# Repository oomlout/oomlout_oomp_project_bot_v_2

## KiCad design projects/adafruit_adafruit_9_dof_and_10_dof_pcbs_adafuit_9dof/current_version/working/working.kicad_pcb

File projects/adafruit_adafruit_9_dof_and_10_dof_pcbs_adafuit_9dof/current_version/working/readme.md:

# adafruit_9_dof_and_10_dof_pcbs
 
## summary 
* id: adafruit_adafruit_9_dof_and_10_dof_pcbs_adafuit_9dof
* user: adafruit
* name: adafruit_9_dof_and_10_dof_pcbs
* board: adafuit_9dof
* repo: https://github.com/adafruit/Adafruit-9-DOF-and-10-DOF-PCBs

* src_file_repo_sch: 
* src_file_repo_sch_link: https://github.com/adafruit/Adafruit-9-DOF-and-10-DOF-PCBs/tree/master/
* full details link: https://github.com/oomlout/oomlout_oomp_project_bot_v_2/tree/main/projects/adafruit_adafruit_9_dof_and_10_dof_pcbs_adafuit_9dof/current_version/working  

## schematic  
  
[schematic (pdf)](working_schematic.pdf) 

## pcb  

[board (pdf)](working.pdf)  

## working_bom
| Id | Designator | Footprint | Quantity | Designation | Supplier and ref |  | None | 
| --- | --- | --- | --- | --- | --- | --- | --- | 
| 1 | C3,C4 | _0805MP | 2 | 0.1uF |  |  | [''] | 
| 2 | FID3,FID2,FID1 | FIDUCIAL_1MM | 3 | FIDUCIAL" |  |  | [''] | 
| 3 | R2,R1,R4,R5,R3,R7,R6 | _0805MP | 7 | 10K |  |  | [''] | 
| 4 | U1 | L3G4200D_LGA16L | 1 | L3GD20 |  |  | [''] | 
| 5 | U$30,U$29,U$31,U$28 | MOUNTINGHOLE_2.5_PLATED_THICK | 4 | MOUNTINGHOLE2.5_THICK |  |  | [''] | 
| 6 | U$32 | ADAFRUIT_3.5MM | 1 |  |  |  | [''] | 
| 7 | Q1,Q2 | SOT23-WIDE | 2 | BSS138 |  |  | [''] | 
| 8 | C2 | _0805MP | 1 | 470nF |  |  | [''] | 
| 9 | U$25 | SYMBOL_GYROXYZ_10MM | 1 |  |  |  | [''] | 
| 10 | JP1 | 1X10_ROUND | 1 |  |  |  | [''] | 
| 11 | C8,C9,C5 | _0805MP | 3 | 10uF |  |  | [''] | 
| 12 | U4 | SOT23-5 | 1 | MIC5225-3.3 |  |  | [''] | 
| 13 | U2 | LGA14 | 1 | LSM303DLHC |  |  | [''] | 
| 14 | U3 | BMP180_EXTENDED | 1 | BMP180 |  |  | [''] | 
| 15 | C7 | _0805MP | 1 | 0.22ÂµF |  |  | [''] | 
| 16 | C6 | _0805MP | 1 | 4.7uF |  |  | [''] | 
| 17 | C1 | _0805MP | 1 | 10nF |  |  | [''] | 
| 18 | U$26 | ADAFRUIT_TEXT_20MM | 1 |  |  |  | [''] | 

## bom_schematic
| Ref | Qnty | Value | Cmp name | Footprint | Description | Vendor | DNP | 
| --- | --- | --- | --- | --- | --- | --- | --- | 
| C1 | 1 | 10nF | CAP_CERAMIC_0805MP | working:_0805MP |  |  |  | 
| C2 | 1 | 470nF | CAP_CERAMIC_0805MP | working:_0805MP |  |  |  | 
| C3, C4 | 2 | 0.1uF | CAP_CERAMIC_0805MP | working:_0805MP |  |  |  | 
| C5, C8, C9 | 3 | 10uF | CAP_CERAMIC_0805MP | working:_0805MP |  |  |  | 
| C6 | 1 | 4.7uF | CAP_CERAMIC_0805MP | working:_0805MP |  |  |  | 
| C7 | 1 | 0.22ÂµF | CAP_CERAMIC_0805MP | working:_0805MP |  |  |  | 
| FID1, FID2, FID3 | 3 | FIDUCIAL"" | FIDUCIAL{dblquote}{dblquote} | working:FIDUCIAL_1MM |  |  |  | 
| JP1 | 1 | HEADER-1X10ROUND | HEADER-1X10ROUND | working:1X10_ROUND |  |  |  | 
| Q1, Q2 | 2 | BSS138 | MOSFET-NWIDE | working:SOT23-WIDE |  |  |  | 
| R1, R2, R3, R4, R5, R6, R7 | 7 | 10K | RESISTOR_0805MP | working:_0805MP |  |  |  | 
| U1 | 1 | L3GD20 | GYRO_L3G2400D | working:L3G4200D_LGA16L |  |  |  | 
| U2 | 1 | LSM303DLHC | LSM303DLHC | working:LGA14 |  |  |  | 
| U3 | 1 | BMP180 | BMP180EXT | working:BMP180_EXTENDED |  |  |  | 
| U4 | 1 | MIC5225-3.3 | VREG_SOT23-5 | working:SOT23-5 |  |  |  | 
| U$28, U$29, U$30, U$31 | 4 | MOUNTINGHOLE2.5_THICK | MOUNTINGHOLE2.5_THICK | working:MOUNTINGHOLE_2.5_PLATED_THICK |  |  |  | 

## mounting_holes
| x | y | package | value | ref | size | 
| --- | --- | --- | --- | --- | --- | 
| 33.02 | 0.0 | MOUNTINGHOLE_2.5_PLATED_THICK | MOUNTINGHOLE2.5_THICK | U$28 | m3 | 
| 33.02 | 17.78 | MOUNTINGHOLE_2.5_PLATED_THICK | MOUNTINGHOLE2.5_THICK | U$29 | m3 | 
| 0.0 | 17.78 | MOUNTINGHOLE_2.5_PLATED_THICK | MOUNTINGHOLE2.5_THICK | U$30 | m3 | 
| 0.0 | 0.0 | MOUNTINGHOLE_2.5_PLATED_THICK | MOUNTINGHOLE2.5_THICK | U$31 | m3 |

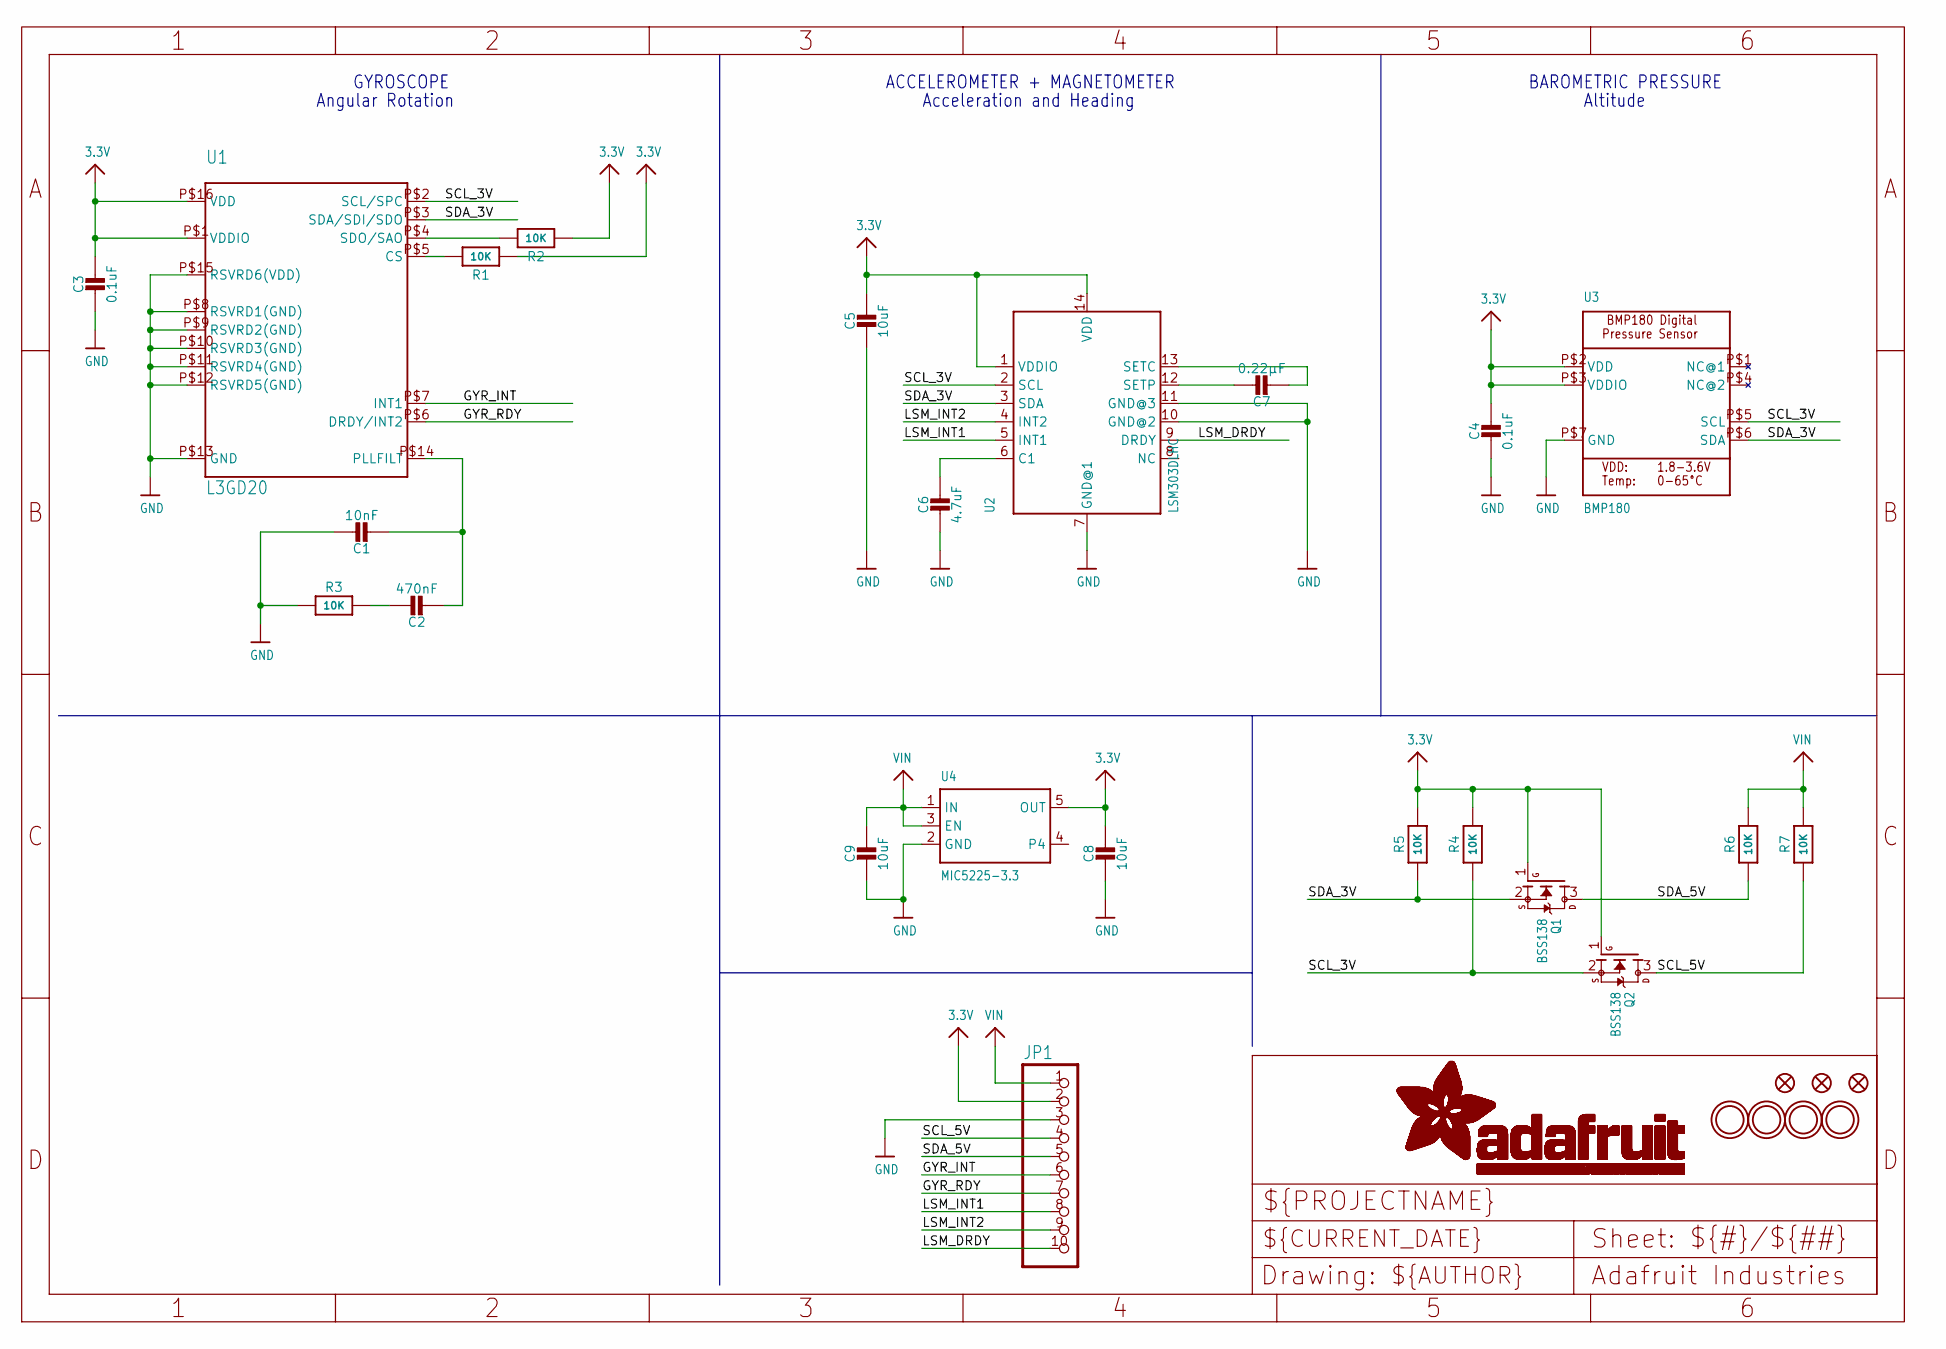
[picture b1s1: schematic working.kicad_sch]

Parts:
C1: 10nF; _0805MP
C2: 470nF; _0805MP
C3, C4: 0.1uF; _0805MP
C5, C8, C9: 10uF; _0805MP
C6: 4.7uF; _0805MP
C7: 0.22µF; _0805MP
FID1, FID2, FID3: FIDUCIAL""; FIDUCIAL_1MM
JP1: HEADER-1X10ROUND; 1X10_ROUND
Q1, Q2: BSS138; SOT23-WIDE
R1, R2, R3, R4, R5, R6, R7: 10K; _0805MP
U1: L3GD20; L3G4200D_LGA16L
U2: LSM303DLHC; LGA14
U3: BMP180; BMP180_EXTENDED
U4: MIC5225-3.3; SOT23-5
U$28, U$29, U$30, U$31: MOUNTINGHOLE2.5_THICK; MOUNTINGHOLE_2.5_PLATED_THICK

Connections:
3.3V: C3.1, C4.1, C5.1, C8.1, JP1.2, Q1.1 (G), Q2.1 (G), R1.1, R2.1, R4.2, R5.2, U1.P$1 (VDDIO), U1.P$16 (VDD), U2.1 (VDDIO), U2.14 (VDD), U3.P$2 (VDD), U3.P$3 (VDDIO), U4.5 (OUT)
GND: C1.1, C3.2, C4.2, C5.2, C6.2, C8.2, C9.2, JP1.3, R3.1, U1.P$8 (RSVRD1(GND)), U1.P$9 (RSVRD2(GND)), U1.P$10 (RSVRD3(GND)), U1.P$11 (RSVRD4(GND)), U1.P$12 (RSVRD5(GND)), U1.P$13 (GND), U1.P$15 (RSVRD6(VDD)), U2.7 (GND@1), U2.10 (GND@2), U2.11 (GND@3), U3.P$7 (GND), U4.2 (GND)
GYR_INT: JP1.6, U1.P$7 (INT1)
GYR_RDY: JP1.7, U1.P$6 (DRDY/INT2)
LSM_DRDY: JP1.10, U2.9 (DRDY)
LSM_INT1: JP1.8, U2.5 (INT1)
LSM_INT2: JP1.9, U2.4 (INT2)
unnamed: R1.2, U1.P$5 (CS)
unnamed: R2.2, U1.P$4 (SDO/SAO)
unnamed: C2.1, R3.2
unnamed: C1.2, C2.2, U1.P$14 (PLLFILT)
unnamed: C7.1, U2.12 (SETP)
unnamed: C6.1, U2.6 (C1)
unnamed: C7.2, U2.13 (SETC)
SCL_3V: Q2.2 (S), R4.1, U1.P$2 (SCL/SPC), U2.2 (SCL), U3.P$5 (SCL)
SCL_5V: JP1.4, Q2.3 (D), R7.1
SDA_3V: Q1.2 (S), R5.1, U1.P$3 (SDA/SDI/SDO), U2.3 (SDA), U3.P$6 (SDA)
SDA_5V: JP1.5, Q1.3 (D), R6.1
VIN: C9.1, JP1.1, R6.2, R7.2, U4.1 (IN), U4.3 (EN)

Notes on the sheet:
Angular Rotation
Acceleration and Heading
ACCELEROMETER + MAGNETOMETER
GYROSCOPE
Altitude
BAROMETRIC PRESSURE

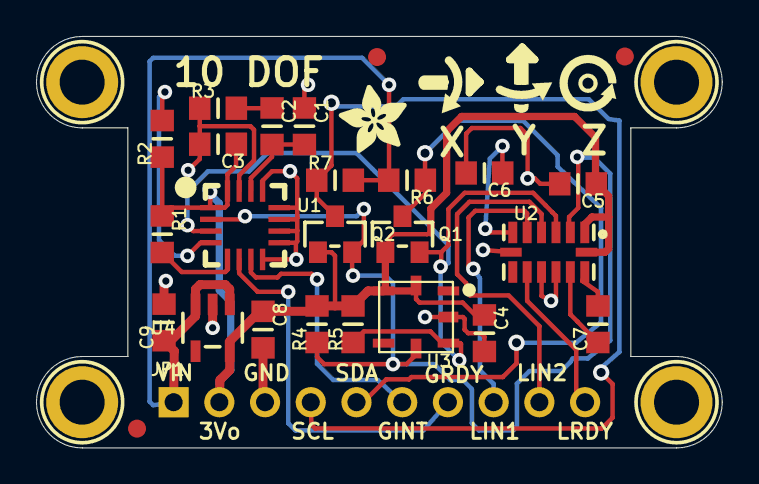
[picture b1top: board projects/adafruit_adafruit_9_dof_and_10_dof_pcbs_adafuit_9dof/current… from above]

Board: 2 copper layers, 38.1 x 22.9 mm, 33 parts (1 on the bottom side), 19 nets.

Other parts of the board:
U$25: SYMBOL_GYROXYZ_10MM
U$26: ADAFRUIT_TEXT_20MM
U$32: ADAFRUIT_3.5MM

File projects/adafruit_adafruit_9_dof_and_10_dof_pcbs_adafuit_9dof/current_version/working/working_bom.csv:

"Id";"Designator";"Footprint";"Quantity";"Designation";"Supplier and ref";
1;"C3,C4";"_0805MP";2;"0.1uF";;;
2;"FID3,FID2,FID1";"FIDUCIAL_1MM";3;"FIDUCIAL""";;;
3;"R2,R1,R4,R5,R3,R7,R6";"_0805MP";7;"10K";;;
4;"U1";"L3G4200D_LGA16L";1;"L3GD20";;;
5;"U$30,U$29,U$31,U$28";"MOUNTINGHOLE_2.5_PLATED_THICK";4;"MOUNTINGHOLE2.5_THICK";;;
6;"U$32";"ADAFRUIT_3.5MM";1;"";;;
7;"Q1,Q2";"SOT23-WIDE";2;"BSS138";;;
8;"C2";"_0805MP";1;"470nF";;;
9;"U$25";"SYMBOL_GYROXYZ_10MM";1;"";;;
10;"JP1";"1X10_ROUND";1;"";;;
11;"C8,C9,C5";"_0805MP";3;"10uF";;;
12;"U4";"SOT23-5";1;"MIC5225-3.3";;;
13;"U2";"LGA14";1;"LSM303DLHC";;;
14;"U3";"BMP180_EXTENDED";1;"BMP180";;;
15;"C7";"_0805MP";1;"0.22µF";;;
16;"C6";"_0805MP";1;"4.7uF";;;
17;"C1";"_0805MP";1;"10nF";;;
18;"U$26";"ADAFRUIT_TEXT_20MM";1;"";;;

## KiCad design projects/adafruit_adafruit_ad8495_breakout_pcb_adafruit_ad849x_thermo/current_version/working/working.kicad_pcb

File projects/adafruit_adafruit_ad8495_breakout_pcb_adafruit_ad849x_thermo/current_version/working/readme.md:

# adafruit_ad8495_breakout_pcb
 
## summary 
* id: adafruit_adafruit_ad8495_breakout_pcb_adafruit_ad849x_thermo
* user: adafruit
* name: adafruit_ad8495_breakout_pcb
* board: adafruit_ad849x_thermo
* repo: https://github.com/adafruit/Adafruit-AD8495-Breakout-PCB

* src_file_repo_sch: 
* src_file_repo_sch_link: https://github.com/adafruit/Adafruit-AD8495-Breakout-PCB/tree/master/
* full details link: https://github.com/oomlout/oomlout_oomp_project_bot_v_2/tree/main/projects/adafruit_adafruit_ad8495_breakout_pcb_adafruit_ad849x_thermo/current_version/working  

## schematic  
  
[schematic (pdf)](working_schematic.pdf) 

## pcb  

[board (pdf)](working.pdf)  

## working_bom
| Id | Designator | Footprint | Quantity | Designation | Supplier and ref |  | None | 
| --- | --- | --- | --- | --- | --- | --- | --- | 
| 1 | R4 | 0805-NO | 1 | 1K |  |  | [''] | 
| 2 | D1 | SOT23-R | 1 | TLVH431 |  |  | [''] | 
| 3 | U$12,U$11 | MOUNTINGHOLE_2.5_PLATED | 2 | MOUNTINGHOLE2.5 |  |  | [''] | 
| 4 | U$9 | SYMBOL_MINUS | 1 |  |  |  | [''] | 
| 5 | FB1 | 0805 | 1 | ferrite |  |  | [''] | 
| 6 | X1 | TERMBLOCK_1X2-3.5MM | 1 | 3.5mm terminal |  |  | [''] | 
| 7 | R3 | 0805-NO | 1 | 1M |  |  | [''] | 
| 8 | U1 | MSOP8_0.65MM | 1 | AD8495ARMZ  |  |  | [''] | 
| 9 | U$10 | ADAFRUIT_2.5MM | 1 |  |  |  | [''] | 
| 10 | R1,R2 | 0805-NO | 2 | 100 |  |  | [''] | 
| 11 | C1 | 0805-NO | 1 | 0.1ÂµF |  |  | [''] | 
| 12 | C4,C2 | 0805-NO | 2 | 0.01uF |  |  | [''] | 
| 13 | FID2,FID1 | FIDUCIAL_1MM | 2 | FIDUCIAL" |  |  | [''] | 
| 14 | C3 | 0805-NO | 1 | 0.1uF |  |  | [''] | 
| 15 | JP1 | 1X04_ROUND | 1 |  |  |  | [''] | 
| 16 | U$8 | SYMBOL_PLUS | 1 |  |  |  | [''] | 
| 17 | U$13 | ADAFRUIT_3.5MM | 1 |  |  |  | [''] | 

## bom_schematic
| Ref | Qnty | Value | Cmp name | Footprint | Description | Vendor | DNP | 
| --- | --- | --- | --- | --- | --- | --- | --- | 
| C1 | 1 | 0.1ÂµF | CAP_CERAMIC0805-NOOUTLINE | working:0805-NO |  |  |  | 
| C2, C4 | 2 | 0.01uF | CAP_CERAMIC0805-NOOUTLINE | working:0805-NO |  |  |  | 
| C3 | 1 | 0.1uF | CAP_CERAMIC0805-NOOUTLINE | working:0805-NO |  |  |  | 
| D1 | 1 | TLVH431 | SHUNT-VREF | working:SOT23-R |  |  |  | 
| FB1 | 1 | ferrite | FERRITE0805 | working:0805 |  |  |  | 
| FID1, FID2 | 2 | FIDUCIAL"" | FIDUCIAL{dblquote}{dblquote} | working:FIDUCIAL_1MM |  |  |  | 
| JP1 | 1 | HEADER-1X4ROUND | HEADER-1X4ROUND | working:1X04_ROUND |  |  |  | 
| R1, R2 | 2 | 100 | RESISTOR0805_NOOUTLINE | working:0805-NO |  |  |  | 
| R3 | 1 | 1M | RESISTOR0805_NOOUTLINE | working:0805-NO |  |  |  | 
| R4 | 1 | 1K | RESISTOR0805_NOOUTLINE | working:0805-NO |  |  |  | 
| U1 | 1 | AD8495ARMZ  | AD849X | working:MSOP8_0.65MM |  |  |  | 
| U$11, U$12 | 2 | MOUNTINGHOLE2.5 | MOUNTINGHOLE2.5 | working:MOUNTINGHOLE_2.5_PLATED |  |  |  | 
| X1 | 1 | 3.5mm terminal | TERMBLOCK_1X2 | working:TERMBLOCK_1X2-3.5MM |  |  |  | 

## mounting_holes
| x | y | package | value | ref | size | 
| --- | --- | --- | --- | --- | --- | 
| 0.0 | 11.43 | MOUNTINGHOLE_2.5_PLATED | MOUNTINGHOLE2.5 | U$11 | m3 | 
| 0.0 | 0.0 | MOUNTINGHOLE_2.5_PLATED | MOUNTINGHOLE2.5 | U$12 | m3 |

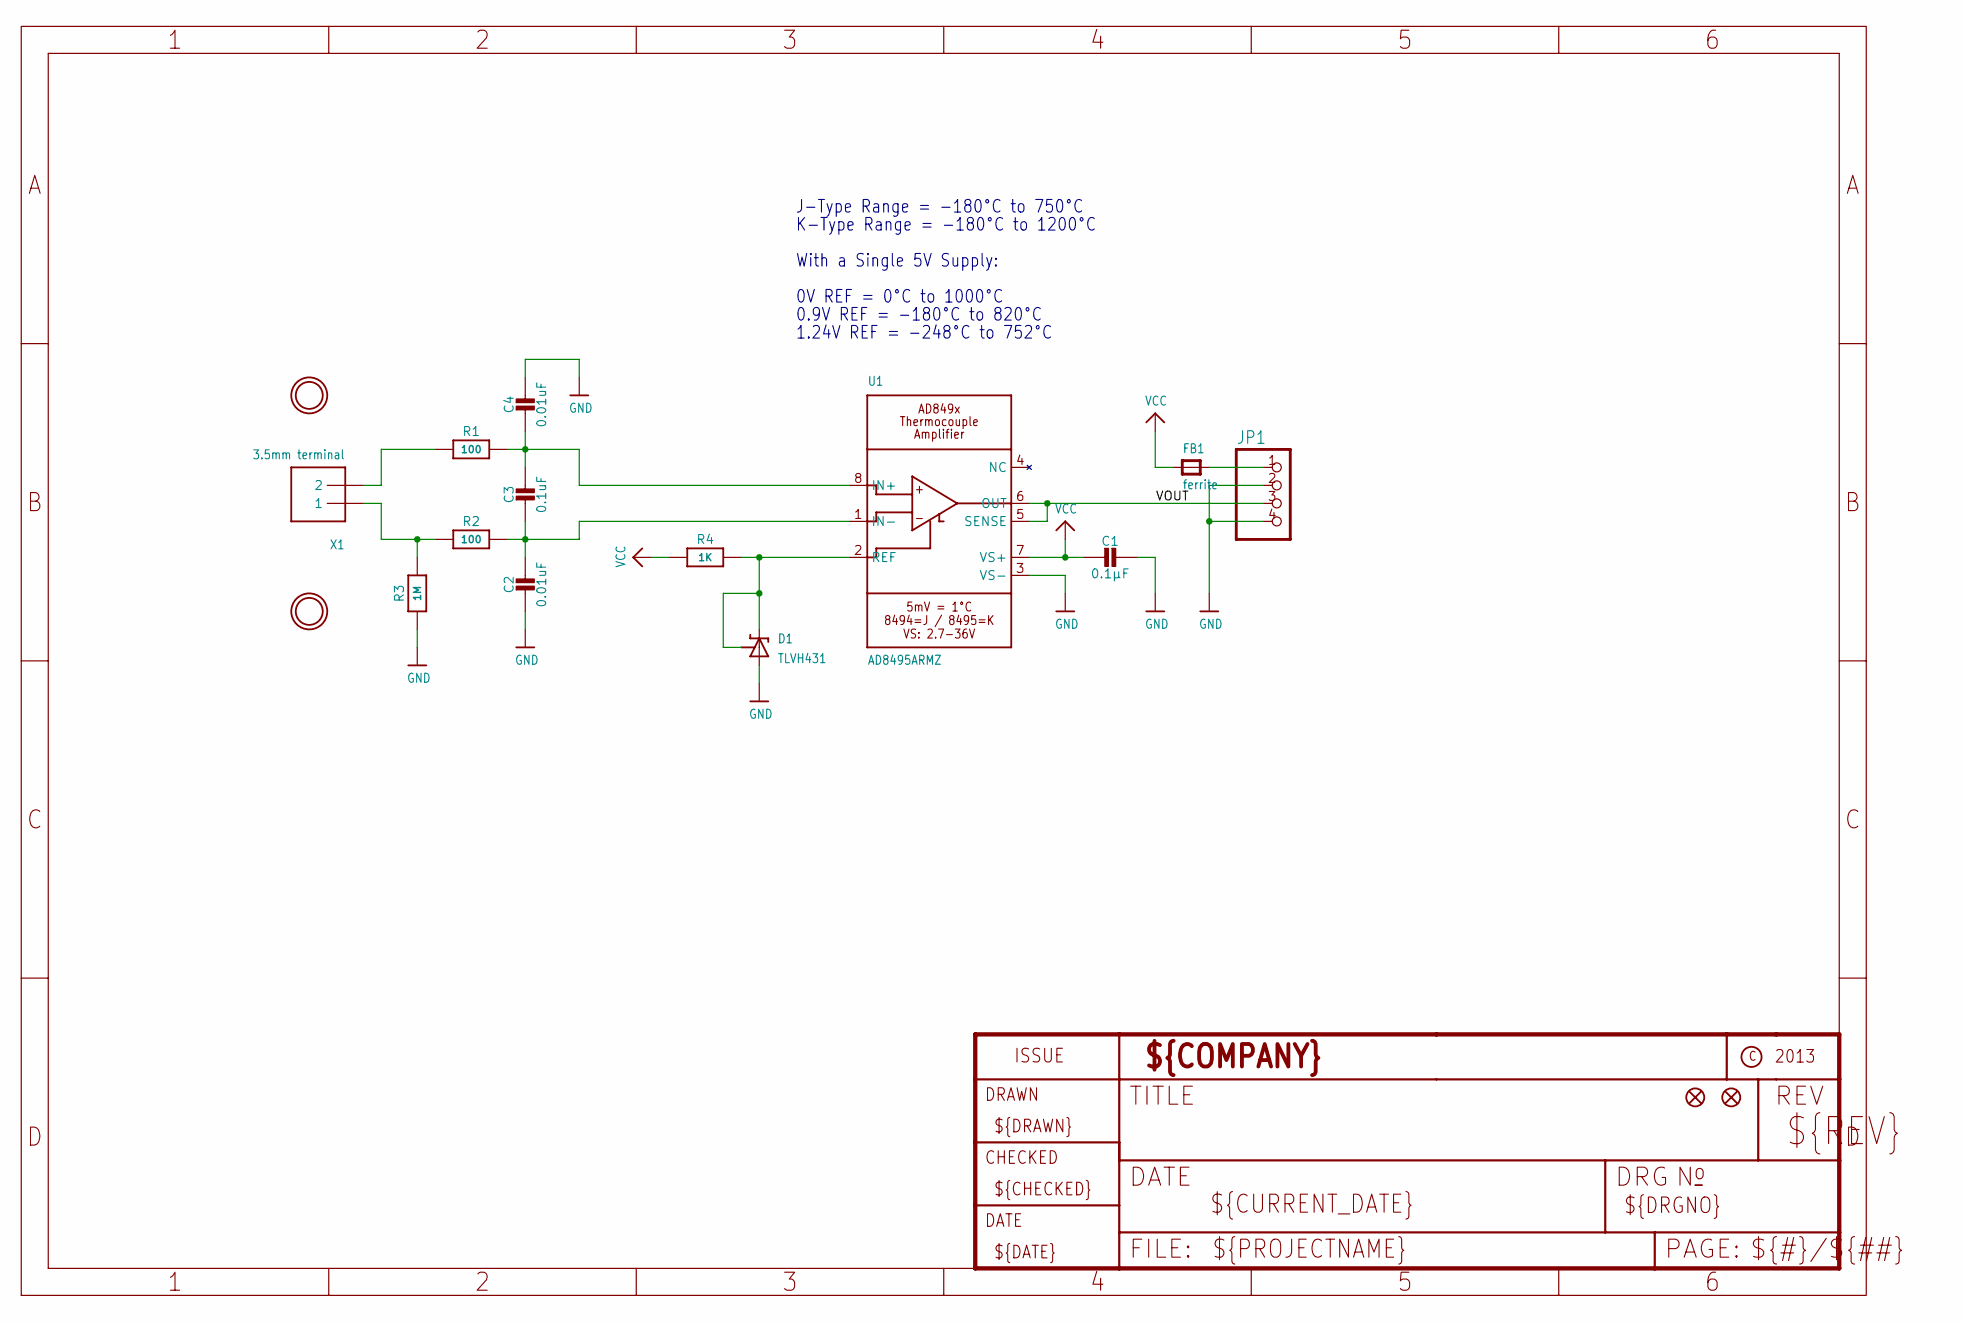
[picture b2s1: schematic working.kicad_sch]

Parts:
C1: 0.1µF; 0805-NO
C2, C4: 0.01uF; 0805-NO
C3: 0.1uF; 0805-NO
D1: TLVH431; SOT23-R
FB1: ferrite; 0805
FID1, FID2: FIDUCIAL""; FIDUCIAL_1MM
JP1: HEADER-1X4ROUND; 1X04_ROUND
R1, R2: 100; 0805-NO
R3: 1M; 0805-NO
R4: 1K; 0805-NO
U1: AD8495ARMZ; MSOP8_0.65MM
U$11, U$12: MOUNTINGHOLE2.5; MOUNTINGHOLE_2.5_PLATED
X1: 3.5mm terminal; TERMBLOCK_1X2-3.5MM

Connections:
GND: C1.1, C2.2, C4.1, D1.3 (A), JP1.2, JP1.4, R3.1, U1.3 (VS-)
IN+: R1.1, X1.2
IN-: R2.1, R3.2, X1.1
unnamed: D1.1 (VREF), D1.2 (C), R4.2, U1.2 (REF)
unnamed: C3.1, C4.2, R1.2, U1.8 (IN+)
unnamed: C2.1, C3.2, R2.2, U1.1 (IN-)
unnamed: FB1.2, JP1.1
VCC: C1.2, FB1.1, R4.1, U1.7 (VS+)
VOUT: JP1.3, U1.5 (SENSE), U1.6 (OUT)

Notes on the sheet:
1.24V REF = -248°C to 752°C
0.9V REF = -180°C to 820°C
K-Type Range = -180°C to 1200°C
0V REF = 0°C to 1000°C
J-Type Range = -180°C to 750°C
With a Single 5V Supply:

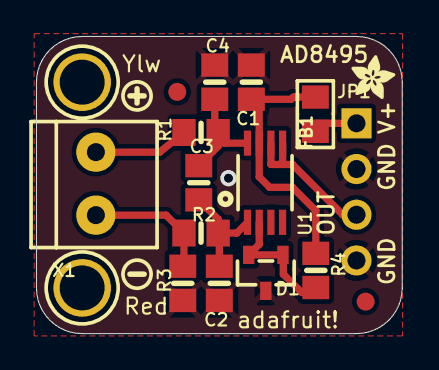
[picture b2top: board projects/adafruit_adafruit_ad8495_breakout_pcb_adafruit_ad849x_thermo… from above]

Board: 2 copper layers, 20.3 x 16.5 mm, 21 parts (1 on the bottom side), 9 nets.

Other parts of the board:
U$8: SYMBOL_PLUS
U$9: SYMBOL_MINUS
U$10: ADAFRUIT_2.5MM
U$13: ADAFRUIT_3.5MM

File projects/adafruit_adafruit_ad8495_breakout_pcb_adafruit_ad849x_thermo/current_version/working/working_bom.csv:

"Id";"Designator";"Footprint";"Quantity";"Designation";"Supplier and ref";
1;"R4";"0805-NO";1;"1K";;;
2;"D1";"SOT23-R";1;"TLVH431";;;
3;"U$12,U$11";"MOUNTINGHOLE_2.5_PLATED";2;"MOUNTINGHOLE2.5";;;
4;"U$9";"SYMBOL_MINUS";1;"";;;
5;"FB1";"0805";1;"ferrite";;;
6;"X1";"TERMBLOCK_1X2-3.5MM";1;"3.5mm terminal";;;
7;"R3";"0805-NO";1;"1M";;;
8;"U1";"MSOP8_0.65MM";1;"AD8495ARMZ ";;;
9;"U$10";"ADAFRUIT_2.5MM";1;"";;;
10;"R1,R2";"0805-NO";2;"100";;;
11;"C1";"0805-NO";1;"0.1µF";;;
12;"C4,C2";"0805-NO";2;"0.01uF";;;
13;"FID2,FID1";"FIDUCIAL_1MM";2;"FIDUCIAL""";;;
14;"C3";"0805-NO";1;"0.1uF";;;
15;"JP1";"1X04_ROUND";1;"";;;
16;"U$8";"SYMBOL_PLUS";1;"";;;
17;"U$13";"ADAFRUIT_3.5MM";1;"";;;

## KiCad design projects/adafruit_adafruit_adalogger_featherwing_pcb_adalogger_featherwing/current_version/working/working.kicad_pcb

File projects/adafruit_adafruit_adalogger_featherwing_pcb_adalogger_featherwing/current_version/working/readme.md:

# adafruit_adalogger_featherwing_pcb
 
## summary 
* id: adafruit_adafruit_adalogger_featherwing_pcb_adalogger_featherwing
* user: adafruit
* name: adafruit_adalogger_featherwing_pcb
* board: adalogger_featherwing
* repo: https://github.com/adafruit/Adafruit-Adalogger-FeatherWing-PCB

* src_file_repo_sch: 
* src_file_repo_sch_link: https://github.com/adafruit/Adafruit-Adalogger-FeatherWing-PCB/tree/master/
* full details link: https://github.com/oomlout/oomlout_oomp_project_bot_v_2/tree/main/projects/adafruit_adafruit_adalogger_featherwing_pcb_adalogger_featherwing/current_version/working  

## schematic  
  
[schematic (pdf)](working_schematic.pdf) 

## pcb  

[board (pdf)](working.pdf)  

## working_bom
| Id | Designator | Footprint | Quantity | Designation | Supplier and ref |  | None | 
| --- | --- | --- | --- | --- | --- | --- | --- | 
| 1 | U$5 | PCBFEAT-REV-040 | 1 |  |  |  | [''] | 
| 2 | MS1 | FEATHERWING_NODIM | 1 | FEATHERWING_NODIM |  |  | [''] | 
| 3 | IC1 | SOIC8_150MIL | 1 | PCF8523T |  |  | [''] | 
| 4 | B1 | CR1220-2 | 1 | cr1220 |  |  | [''] | 
| 5 | R3 | 0603-NO | 1 | 100K |  |  | [''] | 
| 6 | JP1 | 1X11_ROUND | 1 |  |  |  | [''] | 
| 7 | R2,R1 | 0603-NO | 2 | 10K |  |  | [''] | 
| 8 | R4 | 0603-NO | 1 | 1K |  |  | [''] | 
| 9 | JP2 | 1X16_ROUND | 1 |  |  |  | [''] | 
| 10 | FID2,FID1 | FIDUCIAL_1MM | 2 | FIDUCIAL_1MM |  |  | [''] | 
| 11 | Y1 | CRYSTAL_8X3.8 | 1 | 32khz |  |  | [''] | 
| 12 | X4 | MICROSD | 1 | microsd |  |  | [''] | 
| 13 | SJ1 | SOLDERJUMPER_CLOSEDWIRE | 1 |  |  |  | [''] | 
| 14 | JP3,INT1,SDCS0 | 1X01_ROUND | 3 |  |  |  | [''] | 
| 15 | U$4 | ADAFRUIT_3.5MM | 1 |  |  |  | [''] | 
| 16 | SW1 | BTN_KMR2_4.6X2.8 | 1 | KMR2 |  |  | [''] | 
| 17 | C2,C1 | 0805-NO | 2 | 10uF |  |  | [''] | 
| 18 | U$3 | ADALOGGER_LOGO | 1 |  |  |  | [''] | 
| 19 | U$2 | FEATHERLOGO | 1 |  |  |  | [''] | 

## bom_schematic
| Ref | Qnty | Value | Cmp name | Footprint | Description | Vendor | DNP | 
| --- | --- | --- | --- | --- | --- | --- | --- | 
| B1 | 1 | cr1220 | BATTERYCR1220_2 | working:CR1220-2 |  |  |  | 
| C1, C2 | 2 | 10uF | CAP_CERAMIC0805-NOOUTLINE | working:0805-NO |  |  |  | 
| FID1, FID2 | 2 | FIDUCIAL_1MM | FIDUCIAL_1MM | working:FIDUCIAL_1MM |  |  |  | 
| IC1 | 1 | RTC_PCF8523T | RTC_PCF8523T | working:SOIC8_150MIL |  |  |  | 
| INT1 | 1 | HEADER-1X1ROUND | HEADER-1X1ROUND | working:1X01_ROUND |  |  |  | 
| JP1 | 1 | HEADER-1X11 | HEADER-1X11 | working:1X11_ROUND |  |  |  | 
| JP2 | 1 | HEADER-1X16ROUND | HEADER-1X16ROUND | working:1X16_ROUND |  |  |  | 
| JP3 | 1 | HEADER-1X1ROUND | HEADER-1X1ROUND | working:1X01_ROUND |  |  |  | 
| MS1 | 1 | FEATHERWING_NODIM | FEATHERWING_NODIM | working:FEATHERWING_NODIM |  |  |  | 
| R1, R2 | 2 | 10K | RESISTOR_0603_NOOUT | working:0603-NO |  |  |  | 
| R3 | 1 | 100K | RESISTOR_0603_NOOUT | working:0603-NO |  |  |  | 
| R4 | 1 | 1K | RESISTOR_0603_NOOUT | working:0603-NO |  |  |  | 
| SDCS0 | 1 | HEADER-1X1ROUND | HEADER-1X1ROUND | working:1X01_ROUND |  |  |  | 
| SJ1 | 1 | SOLDERJUMPER_CLOSED | SOLDERJUMPER_CLOSED | working:SOLDERJUMPER_CLOSEDWIRE |  |  |  | 
| SW1 | 1 | KMR2 | SWITCH_TACT_SMT4.6X2.8 | working:BTN_KMR2_4.6X2.8 |  |  |  | 
| X4 | 1 | microsd | MICROSD | working:MICROSD |  |  |  | 
| Y1 | 1 | 32khz | CRYSTAL8.0X3.8 | working:CRYSTAL_8X3.8 |  |  |  |

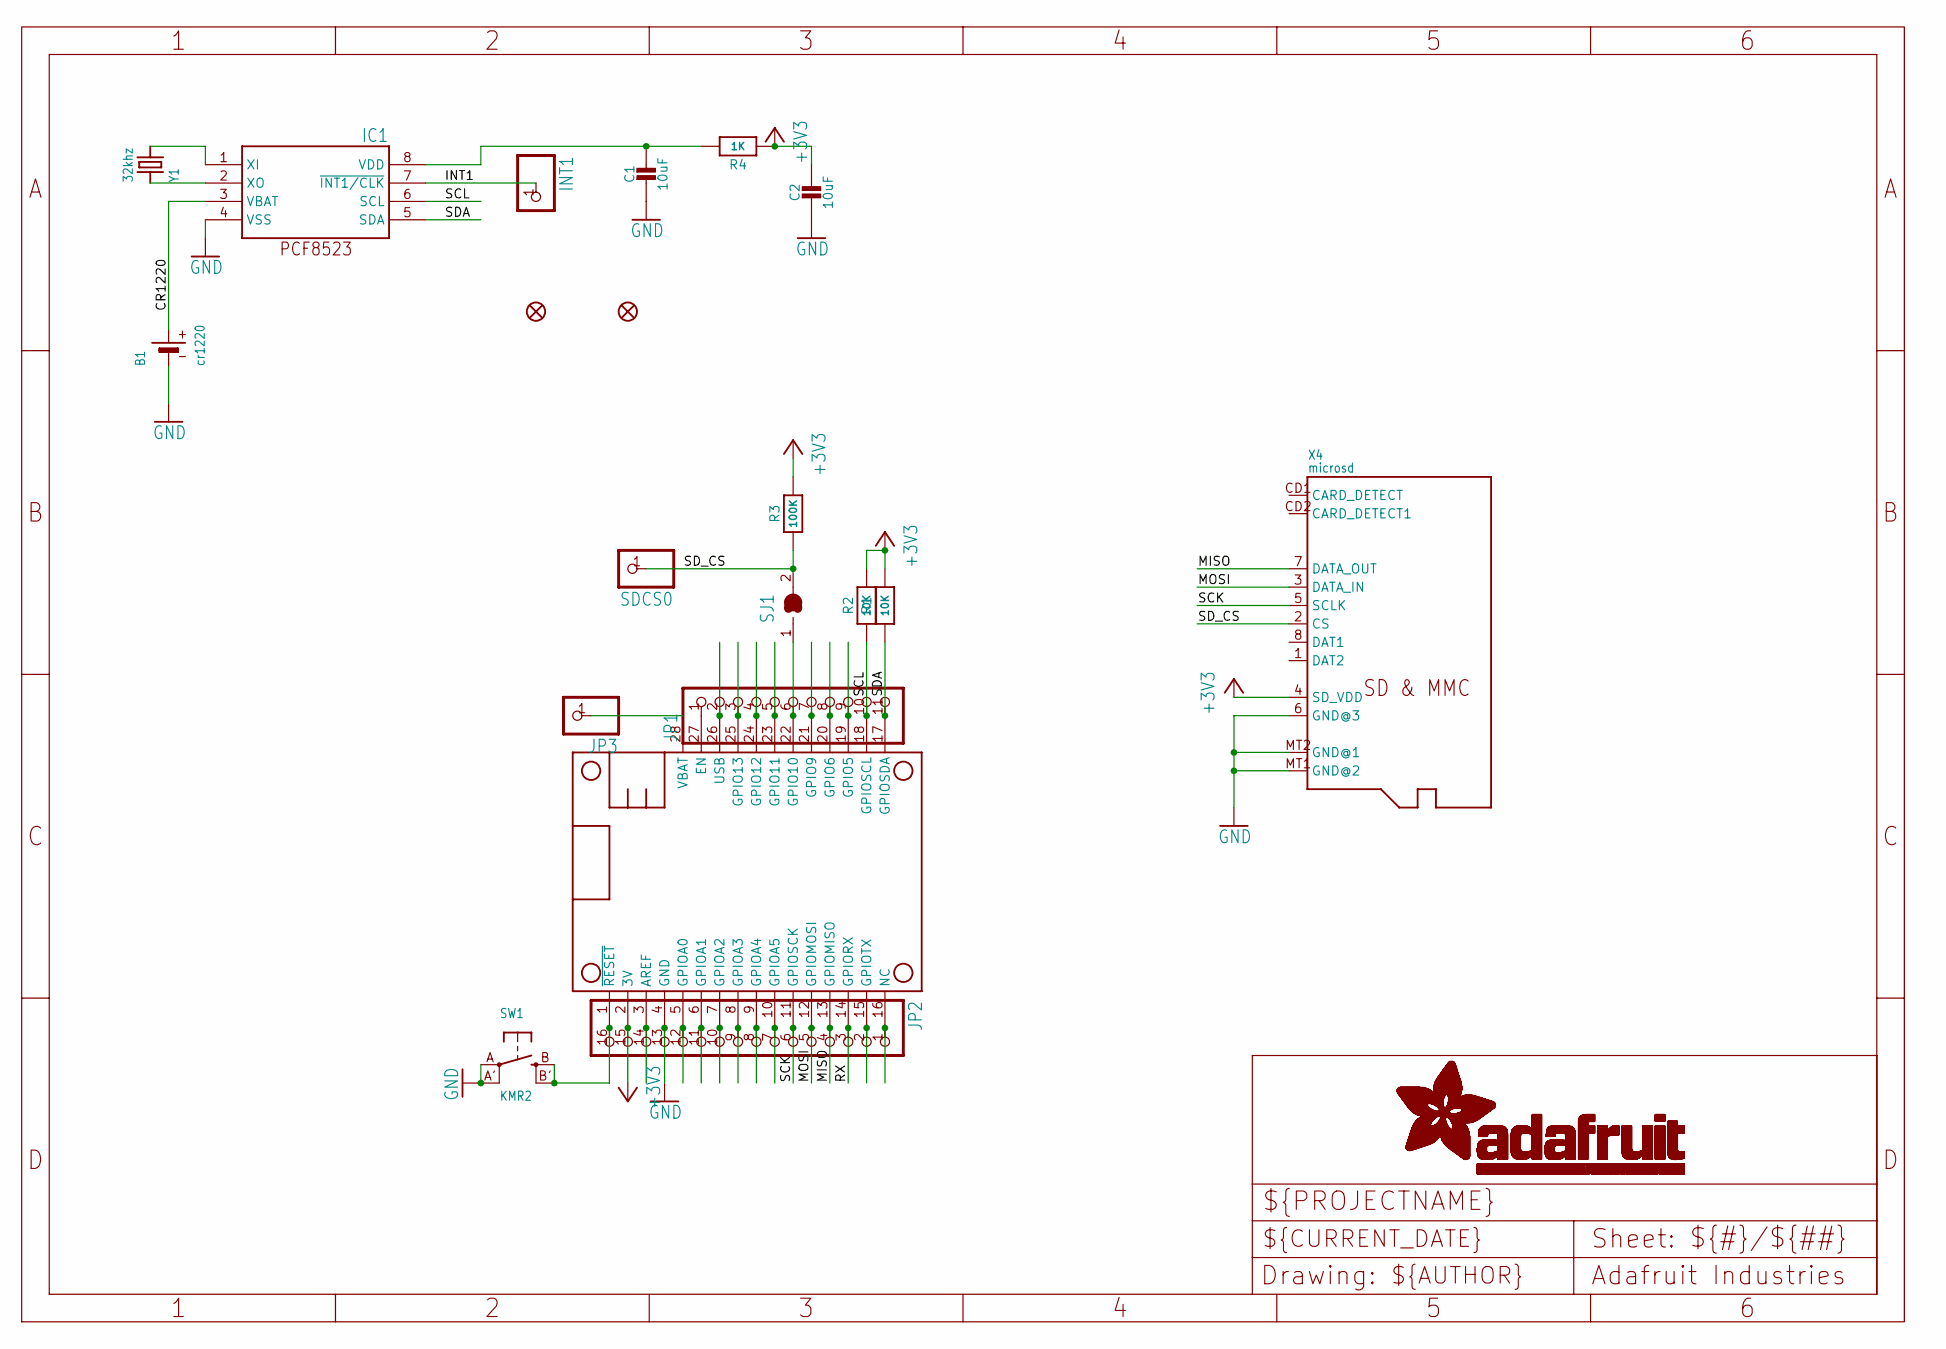
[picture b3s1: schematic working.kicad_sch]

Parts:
B1: cr1220; CR1220-2
C1, C2: 10uF; 0805-NO
FID1, FID2: FIDUCIAL_1MM
IC1: RTC_PCF8523T; SOIC8_150MIL
INT1: HEADER-1X1ROUND; 1X01_ROUND
JP1: HEADER-1X11; 1X11_ROUND
JP2: HEADER-1X16ROUND; 1X16_ROUND
JP3: HEADER-1X1ROUND; 1X01_ROUND
MS1: FEATHERWING_NODIM
R1, R2: 10K; 0603-NO
R3: 100K; 0603-NO
R4: 1K; 0603-NO
SDCS0: HEADER-1X1ROUND; 1X01_ROUND
SJ1: SOLDERJUMPER_CLOSED; SOLDERJUMPER_CLOSEDWIRE
SW1: KMR2; BTN_KMR2_4.6X2.8
X4: microsd; MICROSD
Y1: 32khz; CRYSTAL_8X3.8

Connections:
+3V3: C2.1, JP2.15, MS1.2 (3V), R1.2, R2.2, R3.2, R4.1, X4.4 (SD_VDD)
A: JP2.12, MS1.5 (GPIOA0)
AREF: JP2.14, MS1.3 (AREF)
B: JP2.11, MS1.6 (GPIOA1)
C: JP2.10, MS1.7 (GPIOA2)
CR1220: B1.+, IC1.3 (VBAT)
CS: JP1.6, MS1.22 (GPIO10), SJ1.1
D: JP2.9, MS1.8 (GPIOA3)
E: JP2.8, MS1.9 (GPIOA4)
EN: JP1.1, MS1.27 (EN)
F: JP2.7, MS1.10 (GPIOA5)
G: JP2.1, MS1.16 (NC)
GND: B1.-, C1.2, C2.2, IC1.4 (VSS), JP2.13, MS1.4 (GND), SW1.A, SW1.A' (P1), X4.6 (GND@3), X4.MT1 (GND@2), X4.MT2 (GND@1)
H: JP1.9, MS1.19 (GPIO5)
I: JP1.8, MS1.20 (GPIO6)
INT1: IC1.7 (~INT1/CLK), INT1.1
J: JP1.7, MS1.21 (GPIO9)
L: JP1.5, MS1.23 (GPIO11)
M: JP1.4, MS1.24 (GPIO12)
MISO: JP2.4, MS1.13 (GPIOMISO), X4.7 (DATA_OUT)
MOSI: JP2.5, MS1.12 (GPIOMOSI), X4.3 (DATA_IN)
N: JP1.3, MS1.25 (GPIO13)
unnamed: C1.1, IC1.8 (VDD), R4.2
unnamed: IC1.1 (XI), Y1.P$4 (2)
unnamed: IC1.2 (XO), Y1.P$1 (1)
RESET: JP2.16, MS1.1 (~RESET), SW1.B (S), SW1.B' (S1)
RX: JP2.3, MS1.14 (GPIORX)
SCK: JP2.6, MS1.11 (GPIOSCK), X4.5 (SCLK)
SCL: IC1.6 (SCL), JP1.10, MS1.18 (GPIOSCL), R2.1
SDA: IC1.5 (SDA), JP1.11, MS1.17 (GPIOSDA), R1.1
SD_CS: R3.1, SDCS0.1, SJ1.2, X4.2 (CS)
TX: JP2.2, MS1.15 (GPIOTX)
USB: JP1.2, MS1.26 (USB)
VBAT: JP3.1, MS1.28 (VBAT)

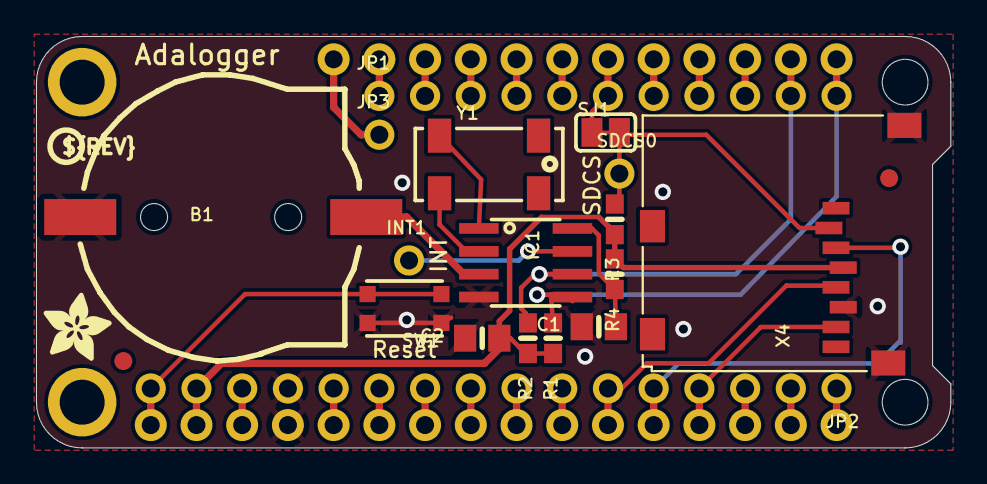
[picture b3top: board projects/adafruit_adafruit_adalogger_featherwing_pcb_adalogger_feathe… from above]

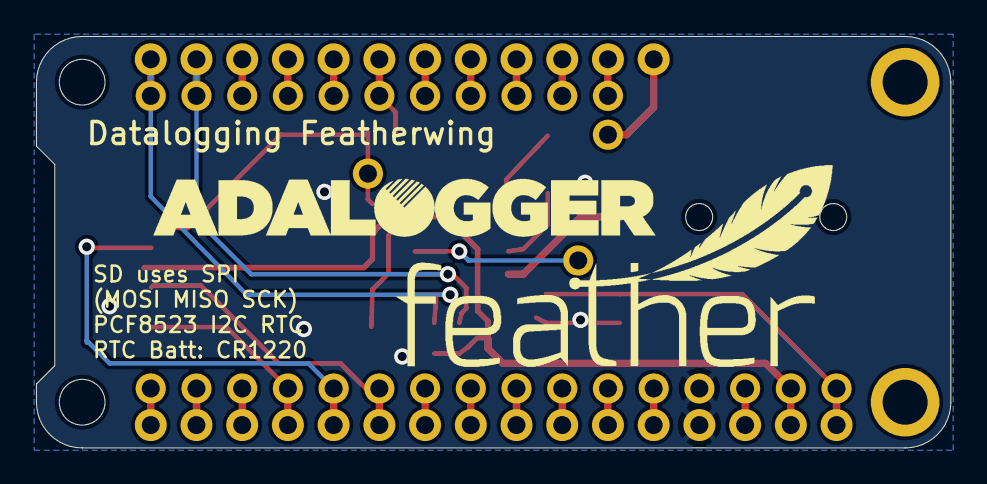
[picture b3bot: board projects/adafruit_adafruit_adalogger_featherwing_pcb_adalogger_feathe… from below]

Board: 2 copper layers, 50.8 x 22.9 mm, 24 parts (2 on the bottom side), 34 nets.

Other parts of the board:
U$2: FEATHERLOGO
U$3: ADALOGGER_LOGO
U$4: ADAFRUIT_3.5MM
U$5: PCBFEAT-REV-040

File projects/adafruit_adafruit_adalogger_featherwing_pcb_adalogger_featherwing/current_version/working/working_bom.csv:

"Id";"Designator";"Footprint";"Quantity";"Designation";"Supplier and ref";
1;"U$5";"PCBFEAT-REV-040";1;"";;;
2;"MS1";"FEATHERWING_NODIM";1;"FEATHERWING_NODIM";;;
3;"IC1";"SOIC8_150MIL";1;"PCF8523T";;;
4;"B1";"CR1220-2";1;"cr1220";;;
5;"R3";"0603-NO";1;"100K";;;
6;"JP1";"1X11_ROUND";1;"";;;
7;"R2,R1";"0603-NO";2;"10K";;;
8;"R4";"0603-NO";1;"1K";;;
9;"JP2";"1X16_ROUND";1;"";;;
10;"FID2,FID1";"FIDUCIAL_1MM";2;"FIDUCIAL_1MM";;;
11;"Y1";"CRYSTAL_8X3.8";1;"32khz";;;
12;"X4";"MICROSD";1;"microsd";;;
13;"SJ1";"SOLDERJUMPER_CLOSEDWIRE";1;"";;;
14;"JP3,INT1,SDCS0";"1X01_ROUND";3;"";;;
15;"U$4";"ADAFRUIT_3.5MM";1;"";;;
16;"SW1";"BTN_KMR2_4.6X2.8";1;"KMR2";;;
17;"C2,C1";"0805-NO";2;"10uF";;;
18;"U$3";"ADALOGGER_LOGO";1;"";;;
19;"U$2";"FEATHERLOGO";1;"";;;

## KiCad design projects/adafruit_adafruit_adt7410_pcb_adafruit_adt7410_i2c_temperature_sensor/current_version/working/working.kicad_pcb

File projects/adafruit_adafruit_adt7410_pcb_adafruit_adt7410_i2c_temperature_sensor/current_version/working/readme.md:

# adafruit_adt7410_pcb
 
## summary 
* id: adafruit_adafruit_adt7410_pcb_adafruit_adt7410_i2c_temperature_sensor
* user: adafruit
* name: adafruit_adt7410_pcb
* board: adafruit_adt7410_i2c_temperature_sensor
* repo: https://github.com/adafruit/Adafruit-ADT7410-PCB

* src_file_repo_sch: 
* src_file_repo_sch_link: https://github.com/adafruit/Adafruit-ADT7410-PCB/tree/master/
* full details link: https://github.com/oomlout/oomlout_oomp_project_bot_v_2/tree/main/projects/adafruit_adafruit_adt7410_pcb_adafruit_adt7410_i2c_temperature_sensor/current_version/working  

## schematic  
  
[schematic (pdf)](working_schematic.pdf) 

## pcb  

[board (pdf)](working.pdf)  

## working_bom
| Id | Designator | Footprint | Quantity | Designation | Supplier and ref |  | None | 
| --- | --- | --- | --- | --- | --- | --- | --- | 
| 1 | R5,R2,R1,R6,R4,R3 | 0603-NO | 6 | 10K |  |  | [''] | 
| 2 | U$16 | ADAFRUIT_3.5MM | 1 |  |  |  | [''] | 
| 3 | JP1 | 1X08_ROUND_70 | 1 |  |  |  | [''] | 
| 4 | C1 | 0603-NO | 1 | 0.1uF |  |  | [''] | 
| 5 | U$4,U$3 | MOUNTINGHOLE_2.0_PLATED | 2 | MOUNTINGHOLE2.0 |  |  | [''] | 
| 6 | U$1 | PCBFEAT-REV-040 | 1 |  |  |  | [''] | 
| 7 | FID1,FID2 | FIDUCIAL_1MM | 2 | FIDUCIAL_1MM |  |  | [''] | 
| 8 | U1 | SOIC8_150MIL | 1 | ADT7410 |  |  | [''] | 
| 9 | C2 | 0805-NO | 1 | 10uF |  |  | [''] | 

## bom_schematic
| Ref | Qnty | Value | Cmp name | Footprint | Description | Vendor | DNP | 
| --- | --- | --- | --- | --- | --- | --- | --- | 
| C1 | 1 | 0.1uF | CAP_CERAMIC0603_NO | working:0603-NO |  |  |  | 
| C2 | 1 | 10uF | CAP_CERAMIC0805-NOOUTLINE | working:0805-NO |  |  |  | 
| FID1, FID2 | 2 | FIDUCIAL_1MM | FIDUCIAL_1MM | working:FIDUCIAL_1MM |  |  |  | 
| JP1 | 1 | HEADER-1X870MIL | HEADER-1X870MIL | working:1X08_ROUND_70 |  |  |  | 
| R1, R2, R3, R4, R5, R6 | 6 | 10K | RESISTOR_0603_NOOUT | working:0603-NO |  |  |  | 
| U1 | 1 | ADT7410 | TEMP_ADT7410 | working:SOIC8_150MIL |  |  |  | 
| U$3, U$4 | 2 | MOUNTINGHOLE2.0 | MOUNTINGHOLE2.0 | working:MOUNTINGHOLE_2.0_PLATED |  |  |  | 

## mounting_holes
| x | y | package | value | ref | size | 
| --- | --- | --- | --- | --- | --- | 
| 0.0 | 0.0 | MOUNTINGHOLE_2.0_PLATED | MOUNTINGHOLE2.0 | U$3 | m3 | 
| 17.78 | 0.0 | MOUNTINGHOLE_2.0_PLATED | MOUNTINGHOLE2.0 | U$4 | m3 |

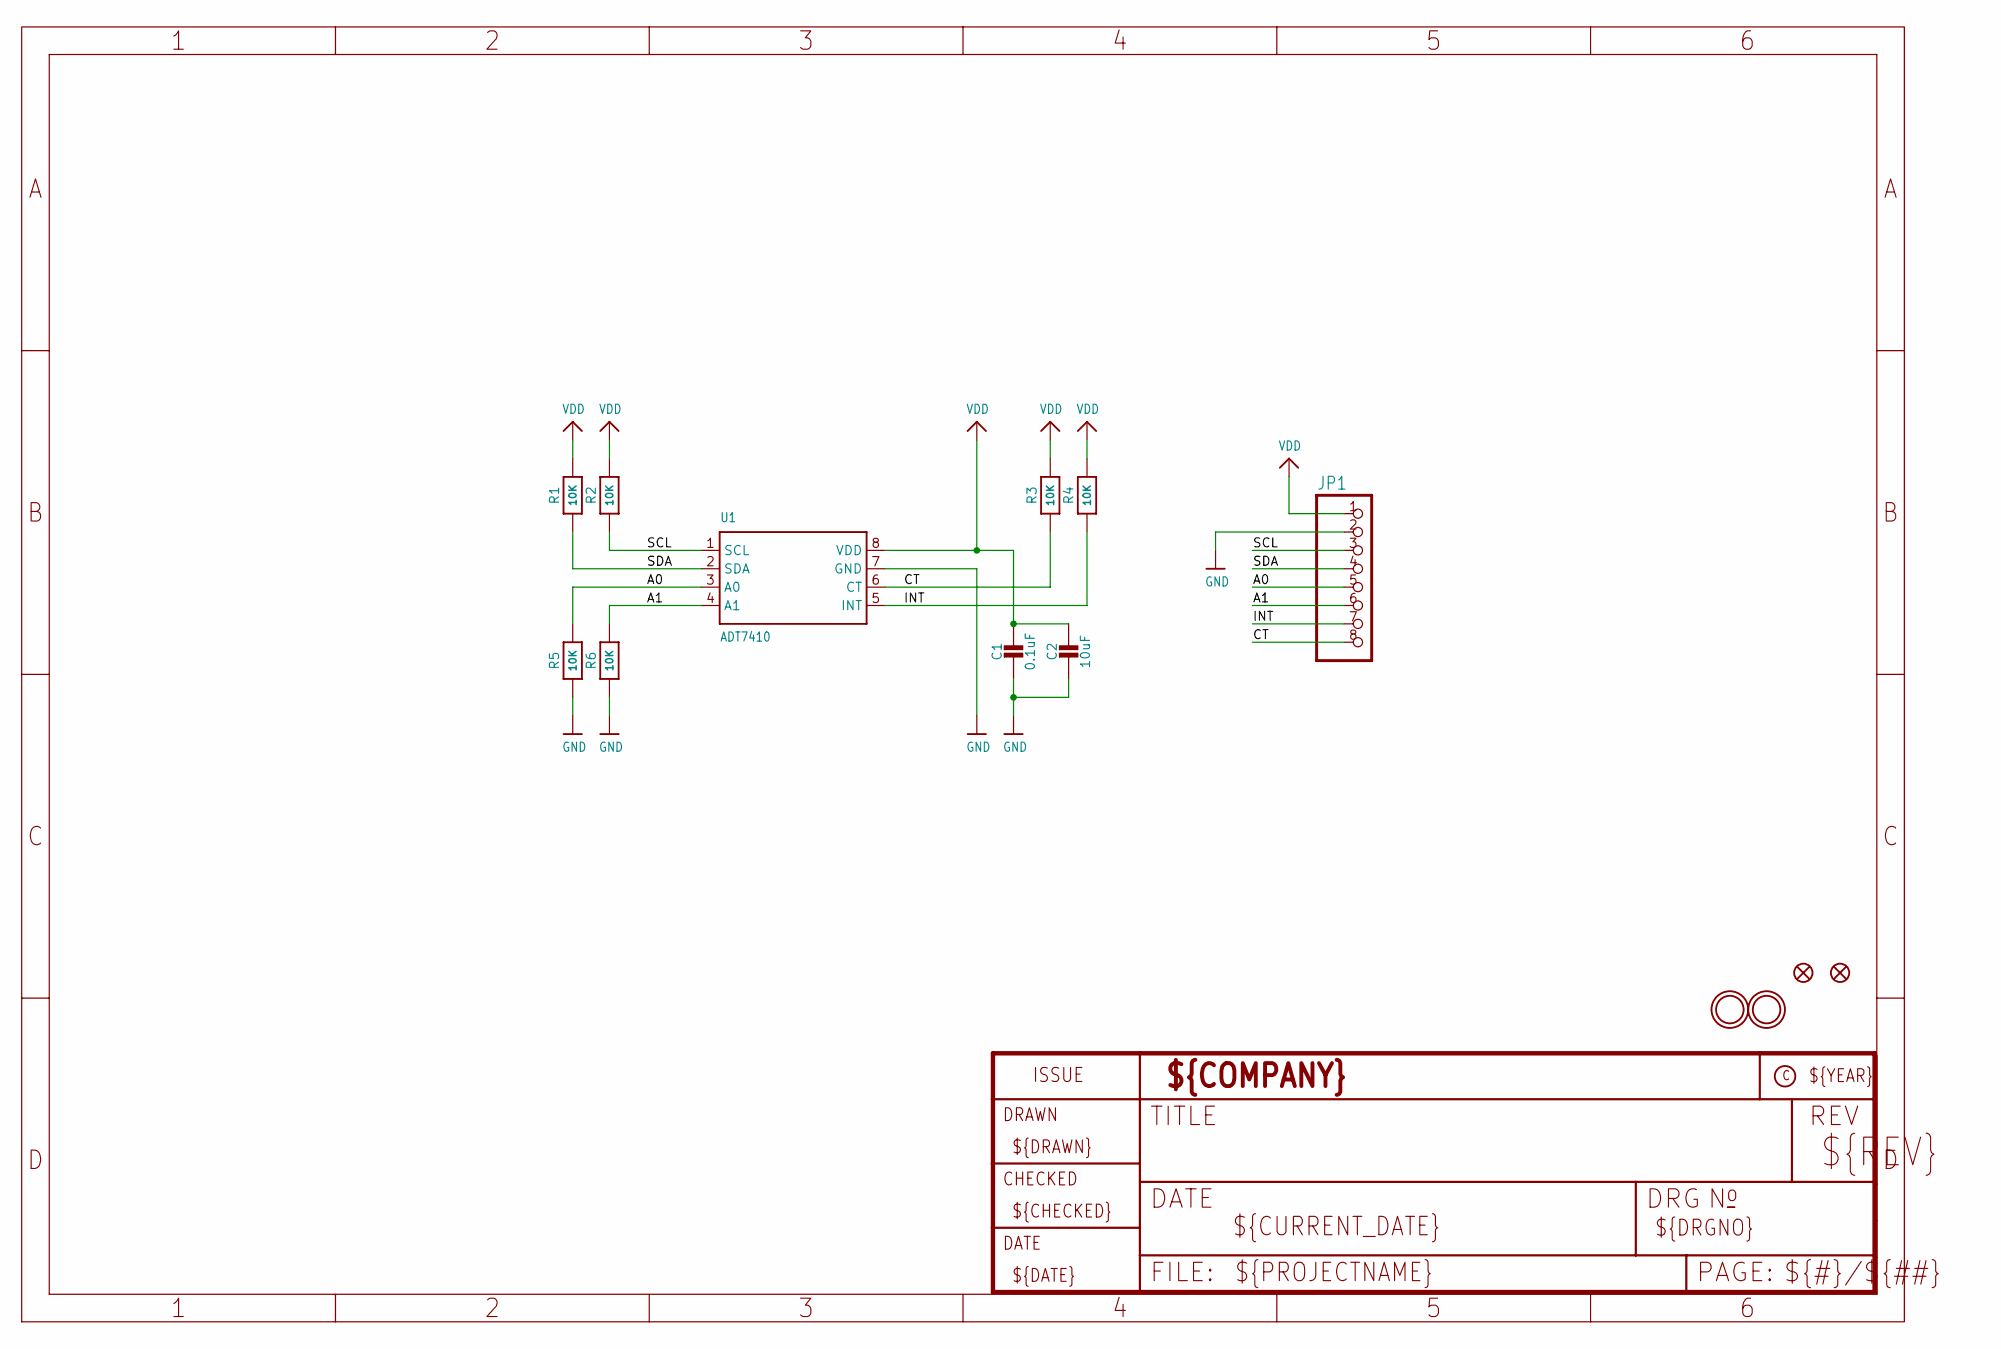
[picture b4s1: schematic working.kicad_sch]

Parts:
C1: 0.1uF; 0603-NO
C2: 10uF; 0805-NO
FID1, FID2: FIDUCIAL_1MM
JP1: HEADER-1X870MIL; 1X08_ROUND_70
R1, R2, R3, R4, R5, R6: 10K; 0603-NO
U1: ADT7410; SOIC8_150MIL
U$3, U$4: MOUNTINGHOLE2.0; MOUNTINGHOLE_2.0_PLATED

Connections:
A0: JP1.5, R5.2, U1.3 (A0)
A1: JP1.6, R6.2, U1.4 (A1)
CT: JP1.8, R3.1, U1.6 (CT)
GND: C1.2, C2.2, JP1.2, R5.1, R6.1, U1.7 (GND)
INT: JP1.7, R4.1, U1.5 (INT)
SCL: JP1.3, R2.1, U1.1 (SCL)
SDA: JP1.4, R1.1, U1.2 (SDA)
VDD: C1.1, C2.1, JP1.1, R1.2, R2.2, R3.2, R4.2, U1.8 (VDD)

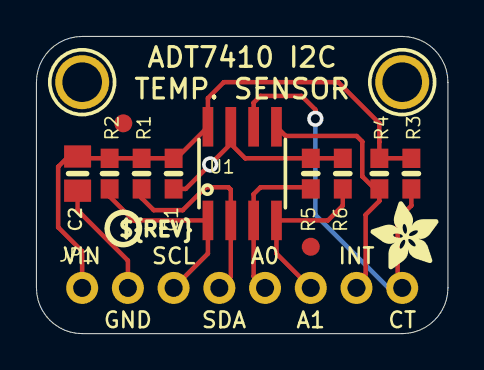
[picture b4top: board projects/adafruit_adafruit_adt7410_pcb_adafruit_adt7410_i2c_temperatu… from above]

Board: 2 copper layers, 22.9 x 16.5 mm, 16 parts (0 on the bottom side), 8 nets.

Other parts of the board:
U$1: PCBFEAT-REV-040
U$16: ADAFRUIT_3.5MM

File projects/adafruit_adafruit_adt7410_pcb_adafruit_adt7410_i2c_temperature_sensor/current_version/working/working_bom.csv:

"Id";"Designator";"Footprint";"Quantity";"Designation";"Supplier and ref";
1;"R5,R2,R1,R6,R4,R3";"0603-NO";6;"10K";;;
2;"U$16";"ADAFRUIT_3.5MM";1;"";;;
3;"JP1";"1X08_ROUND_70";1;"";;;
4;"C1";"0603-NO";1;"0.1uF";;;
5;"U$4,U$3";"MOUNTINGHOLE_2.0_PLATED";2;"MOUNTINGHOLE2.0";;;
6;"U$1";"PCBFEAT-REV-040";1;"";;;
7;"FID1,FID2";"FIDUCIAL_1MM";2;"FIDUCIAL_1MM";;;
8;"U1";"SOIC8_150MIL";1;"ADT7410";;;
9;"C2";"0805-NO";1;"10uF";;;
